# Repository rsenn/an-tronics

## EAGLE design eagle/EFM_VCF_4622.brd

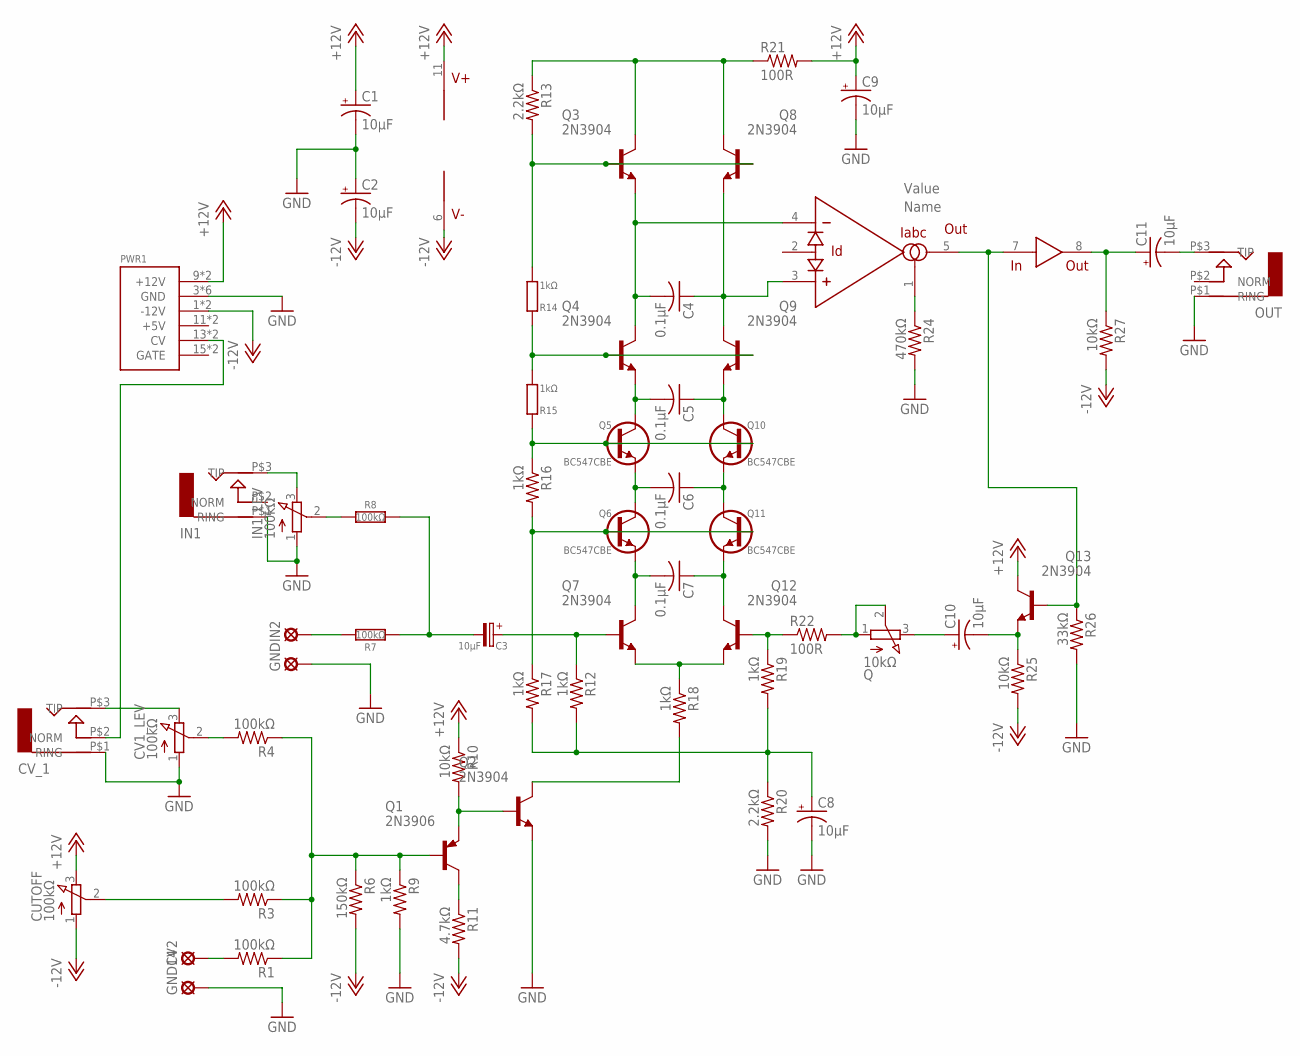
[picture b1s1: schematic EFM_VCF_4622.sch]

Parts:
C1, C2, C8, C9: 10μF; B45181A
C3: 10μF; E2,5-4
C4, C5, C6, C7: 0.1μF; C050-025X075
C10: 10μF; B45181C
C11: 10μF; B45181B
CUTOFF: 100kΩ; 3RP/1610N
CV1_LEV: 100kΩ; 3RP/1610N
CV2: LSP10
CV_1: AUDIO-JACK; ERTHENVAR-JACK-90DEG
GND, GND14: LSP10
IC1: LM13700N; DIL16
IN1: AUDIO-JACK; ERTHENVAR-JACK-90DEG
IN1_LEV: 100kΩ; 3RP/1610N
IN2: LSP10
OUT: AUDIO-JACK; ERTHENVAR-JACK-90DEG
PWR1: POWER; POWER_16
Q: 10kΩ; 3RP/1610N
Q1: 2N3906; TO92
Q2, Q3, Q4, Q7, Q8, Q9, Q12, Q13: 2N3904; TO92
Q5, Q6, Q10, Q11: BC547CBE; TO92-CBE
R1, R3, R4: 100kΩ; 0207/7
R6: 150kΩ; 0207/7
R7, R8: 100kΩ; 0204/10
R9, R12, R16, R17, R18, R19: 1kΩ; 0207/7
R10, R25, R27: 10kΩ; 0207/7
R11: 4.7kΩ; 0207/7
R13, R20: 2.2kΩ; 0207/7
R14, R15: 1kΩ; 0204/10-V
R21, R22: 100R; 0207/7
R24: 470kΩ; 0207/7
R26: 33kΩ; 0207/7

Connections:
+12V: C1.+, C9.+, CUTOFF.3 (E), IC1.11 (V+), PWR1.9 (+12V), PWR1.10 (+12V), Q13.1 (C), R10.1, R21.2
-12V: C2.-, CUTOFF.1 (A), IC1.6 (V-), PWR1.1 (-12V), PWR1.2 (-12V), R6.2, R11.2, R25.2, R27.2
GND: C1.-, C2.+, C8.-, C9.-, CV1_LEV.1 (A), CV_1.P$1 (RING), GND.MP, GND14.MP, IN1.P$1 (RING), IN1_LEV.1 (A), OUT.P$1 (RING), PWR1.3 (GND), PWR1.4 (GND), PWR1.5 (GND), PWR1.6 (GND), PWR1.7 (GND), PWR1.8 (GND), Q2.3 (E), R9.2, R20.2, R24.2, R26.2
unnamed: IC1.1 (IABC), R24.1
unnamed: Q.1 (A), Q.2 (S), R22.2
unnamed: Q2.1 (C), R18.2
unnamed: Q7.3 (E), Q12.3 (E), R18.1
unnamed: IN2.MP, R7.2
unnamed: C3.-, R7.1, R8.2
unnamed: C3.+, Q7.2 (B), R12.1
unnamed: Q1.3 (E), Q2.2 (B), R10.2
unnamed: C4.2, IC1.4 (-IN), Q3.3 (E), Q4.1 (C)
unnamed: C10.+, Q.3 (E)
unnamed: CV2.MP, R1.2
unnamed: C4.1, IC1.3 (+IN), Q8.3 (E), Q9.1 (C)
unnamed: C6.1, Q10.E, Q11.C
unnamed: C5.2, Q4.3 (E), Q5.C
unnamed: C5.1, Q9.3 (E), Q10.C
unnamed: C7.1, Q11.E, Q12.1 (C)
unnamed: C7.2, Q6.E, Q7.1 (C)
unnamed: IC1.5 (OUT), IC1.7 (IN), Q13.2 (B), R26.1
unnamed: Q1.2 (B), R1.1, R3.1, R4.1, R6.1, R9.1
unnamed: C8.+, R12.2, R17.2, R19.2, R20.1
unnamed: Q12.2 (B), R19.1, R22.1
unnamed: Q1.1 (C), R11.1
unnamed: C11.+, IC1.8 (OUT), R27.1
unnamed: C6.2, Q5.E, Q6.C
unnamed: C11.-, OUT.P$3 (TIP)
unnamed: C10.-, Q13.3 (E), R25.1
unnamed: Q3.1 (C), Q8.1 (C), R13.1, R21.1
unnamed: Q3.2 (B), Q8.2 (B), R13.2, R14.2 (1)
unnamed: Q4.2 (B), Q9.2 (B), R14.1 (2), R15.2 (1)
unnamed: Q5.B, Q10.B, R15.1 (2), R16.1
unnamed: Q6.B, Q11.B, R16.2, R17.1
unnamed: CV1_LEV.2 (S), R4.2
unnamed: CV_1.P$2 (NORM), PWR1.13 (CV), PWR1.14 (CV)
unnamed: CUTOFF.2 (S), R3.2
unnamed: IN1_LEV.2 (S), R8.1
unnamed: IN1.P$3 (TIP), IN1_LEV.3 (E)
unnamed: CV1_LEV.3 (E), CV_1.P$3 (TIP)

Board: 2 copper layers, 61 parts (0 on the bottom side), 40 nets, no tracks yet.

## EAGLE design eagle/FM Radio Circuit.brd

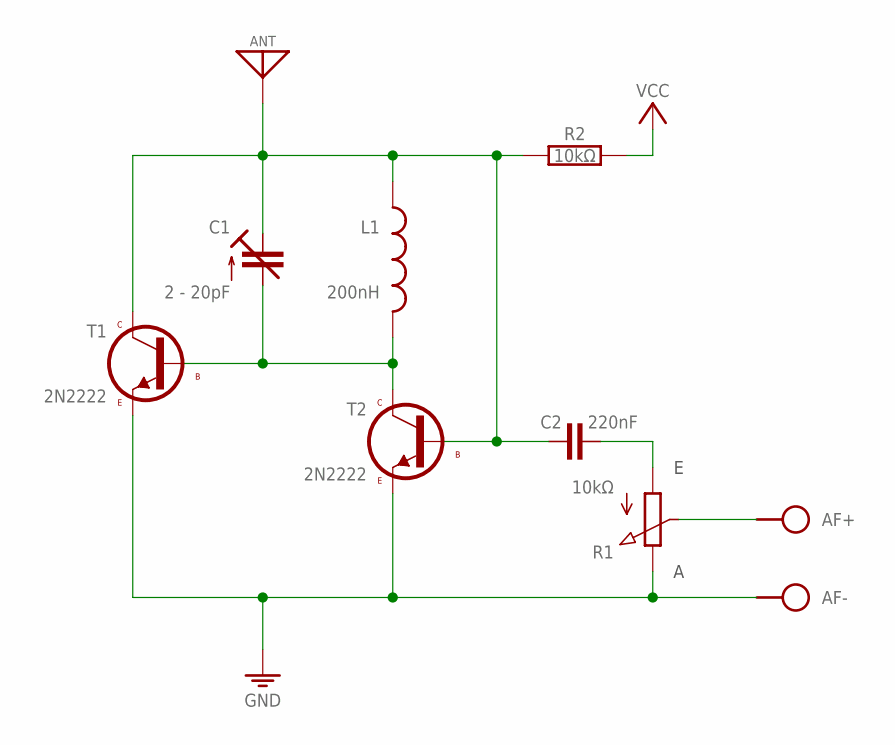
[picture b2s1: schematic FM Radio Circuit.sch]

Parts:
AF: SPAD+-+-; SPAD+-
ANT: ANT; SPAD
BAT: VCC_GNDL; SPAD-+
C1: 2 - 20pF; TRIM-2222-808
C2: 220nF; C050-020X044
L1: 200nH; L-04/7-V
R1: 10kΩ; POT
R2: 10kΩ; 0204/10
T1, T2: 2N2222; TO92-EBC

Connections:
GND: AF.1, BAT.1 (GND), R1.E, T1.E, T2.E
unnamed: C1.2 (A), L1.2, T1.B, T2.C
unnamed: C2.2, R1.A
unnamed: ANT.1, C1.3 (E), C2.1, L1.1, R2.1, T1.C, T2.B
unnamed: AF.2, R1.S
VCC: BAT.2 (VCC), R2.2

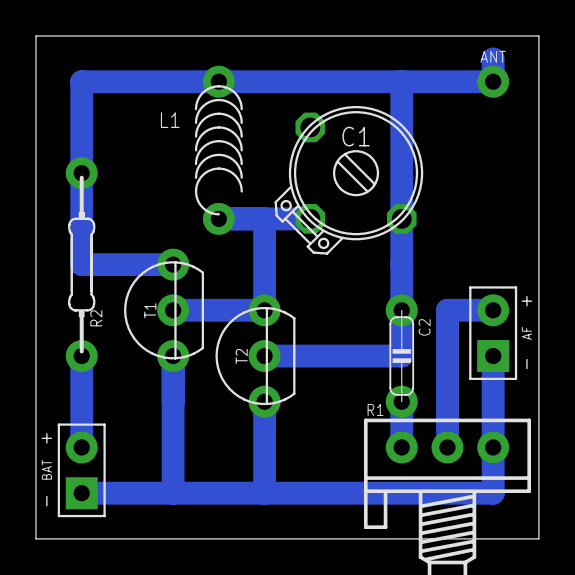
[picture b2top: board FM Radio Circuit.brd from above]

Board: 2 copper layers, 27.9 x 27.9 mm, 10 parts (0 on the bottom side), 6 nets.

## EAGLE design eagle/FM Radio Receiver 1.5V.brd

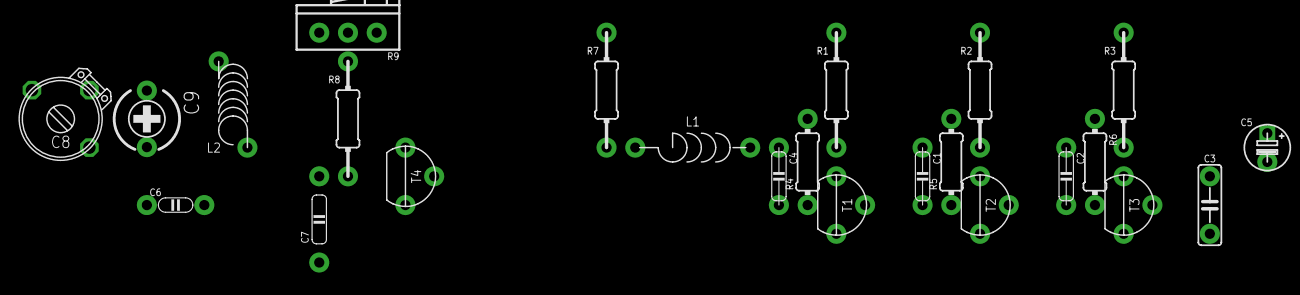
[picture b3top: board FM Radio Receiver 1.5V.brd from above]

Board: 2 copper layers, 24 parts (0 on the bottom side), 14 nets, no tracks yet.

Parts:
C1, C2: C050-020X044
C3: 10nF; C050-025X060
C4: 10nF; C050-020X044
C5: 100μF; E2.5-4/V
C6: 22pF; C050-020X036
C7: 100nF; C075-020X044
C8: 20pF; TRIM-2222-808
C9: 5pF; CTRIMTZ03
L1: 2.2μH; L-03/10
L2: L-04/8V
R1, R2: 4.7kΩ; 0204/10-V
R3: 0204/10-V
R4, R5: 1MΩ; 0204/7
R6: 56kΩ; 0204/7
R7: 10kΩ; 0204/10-V
R8: 470kΩ; 0204/10-V
R9: 10kΩ; POT
T1, T2, T3, T4: TO92-CBE-A

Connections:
unnamed: C1.2, R5.1, T2.2
unnamed: C2.1, R2.2, R5.2, T2.1
unnamed: C1.1, R1.2, R4.2, T1.1
unnamed: C2.2, R6.1, T3.2
unnamed: C3.1, R3.2, R6.2, T3.1
unnamed: C4.2, R4.1, T1.2
unnamed: C4.1, L1.1
unnamed: C5.+, R1.1, R2.1, R3.1, R7.1, R9.A
unnamed: C7.2, R8.2, T4.2
unnamed: R8.1, R9.S
unnamed: C8.2, C9.2, L2.2, T4.1
unnamed: C6.2, C7.1, L1.2, L2.1, R7.2
unnamed: C6.1, C8.1, C9.1
unnamed: C3.2, C5.-, R9.E, T1.3, T2.3, T3.3, T4.3

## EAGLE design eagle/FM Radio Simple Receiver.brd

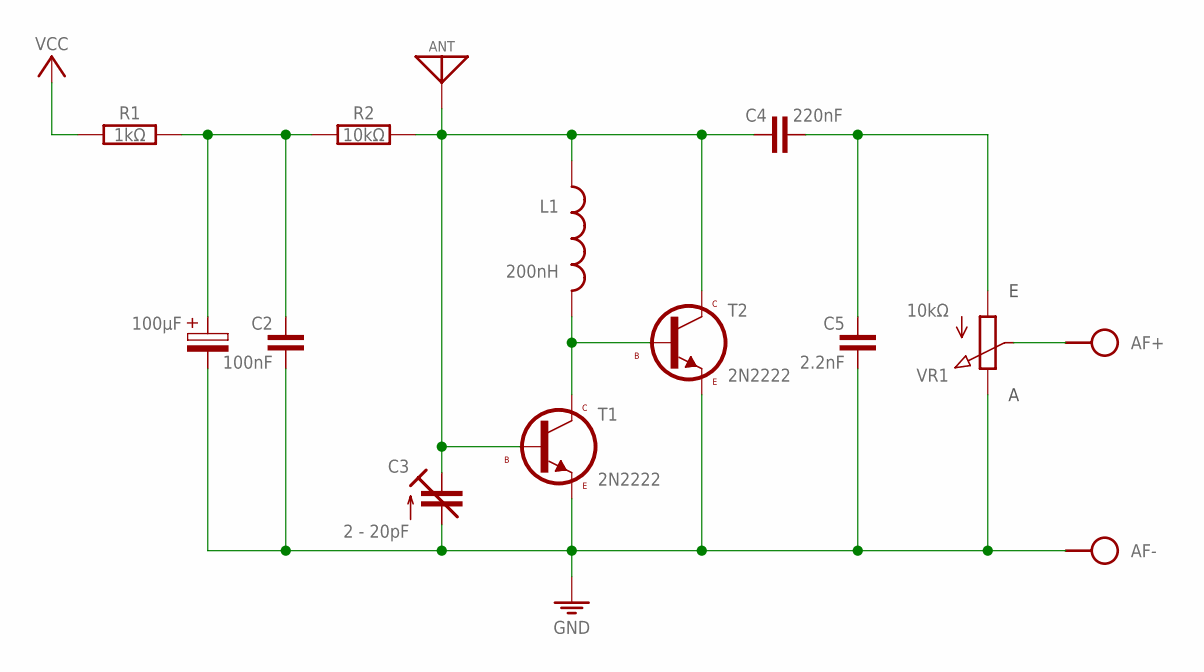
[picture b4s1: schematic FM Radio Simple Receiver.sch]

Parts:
100µF: CPOLE2,5-5/V; E2,5-5/V
AF: SPAD+-+-; SPAD+-
ANT: ANT; SPAD
BAT: VCC_GNDL; SPAD-+
C2: 100nF; C050-020X036/V
C3: 2 - 20pF; TRIM-2222-808
C4: 220nF; C050-020X044
C5: 2.2nF; C050-020X036/V
L1: 200nH; L-04/7-V
R1: 1kΩ; 0204/10
R2: 10kΩ; 0204/10
T1, T2: 2N2222; TO92-EBC
VR1: 10kΩ; POT

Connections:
GND: 100µF.-, AF.1, BAT.1 (GND), C2.2, C3.1 (A), C3.3 (A), C5.2, T1.E, T2.E, VR1.E
unnamed: ANT.1, C3.2 (E), C4.1, L1.1, R2.2, T1.B, T2.C
unnamed: 100µF.+, C2.1, R1.2, R2.1
unnamed: C4.2, C5.1, VR1.A
unnamed: L1.2, T1.C, T2.B
unnamed: AF.2, VR1.S
VCC: BAT.2 (VCC), R1.1

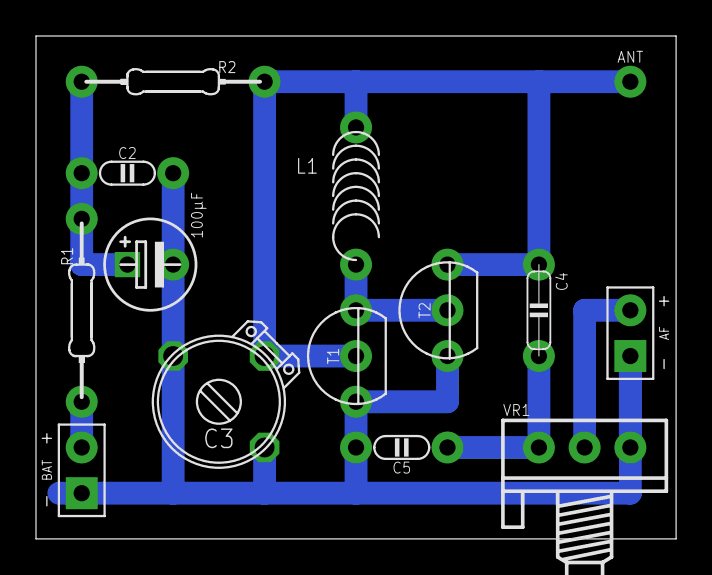
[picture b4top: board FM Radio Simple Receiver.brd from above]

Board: 2 copper layers, 35.6 x 27.9 mm, 14 parts (0 on the bottom side), 7 nets.

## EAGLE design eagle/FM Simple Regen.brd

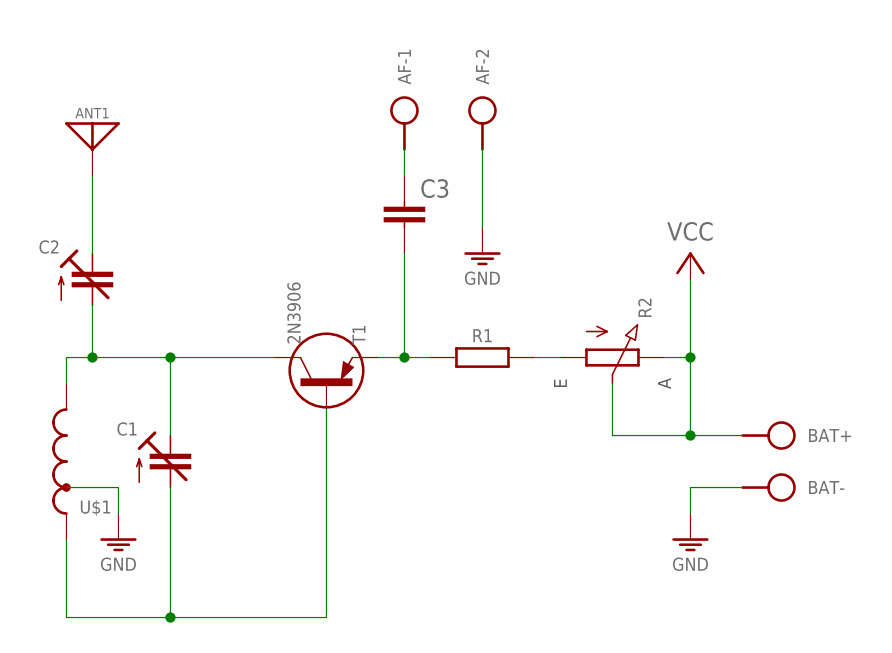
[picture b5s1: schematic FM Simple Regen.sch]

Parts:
AF: SPAD-2
ANT1: ANT; SPAD
BAT+: SPAD
BAT-: SPAD
C1: C-TR-PH201272222-808-2PINB; TRIM-2222-808
C2: C-TR-PH201272222-808-2PIN; TRIM-2222-808
C3: C050-024X044
R1: R-H0204/10; 0204/10
R2: POT
T1: 2N3906; TO92
U$1: L-TAP104/7; L-04/7-TAP1

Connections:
GND: AF.2, BAT-.1, U$1.T
unnamed: C1.2 (A), T1.2 (B), U$1.1
unnamed: AF.1, C3.1
unnamed: C1.3 (E), C2.2 (A), T1.3 (C), U$1.2
unnamed: C3.2, R1.1, T1.1 (E)
unnamed: R1.2, R2.A
unnamed: ANT1.1, C2.1 (E)
VCC: BAT+.1, R2.E, R2.S

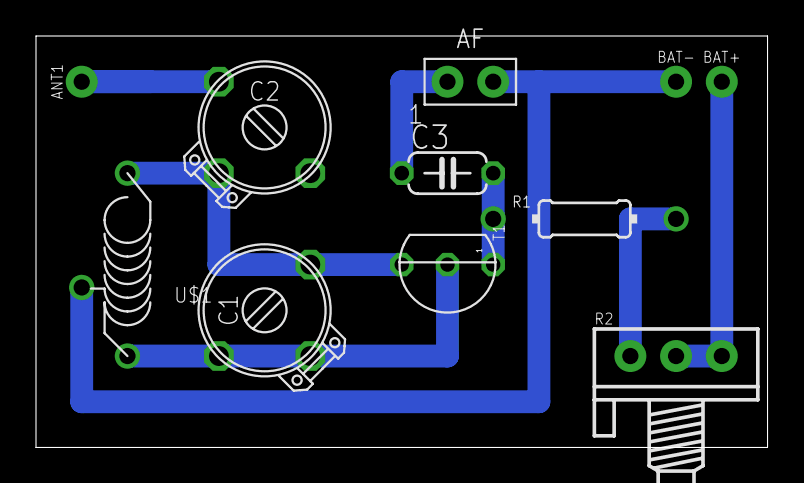
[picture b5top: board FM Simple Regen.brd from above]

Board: 2 copper layers, 40.6 x 22.9 mm, 11 parts (0 on the bottom side), 8 nets.

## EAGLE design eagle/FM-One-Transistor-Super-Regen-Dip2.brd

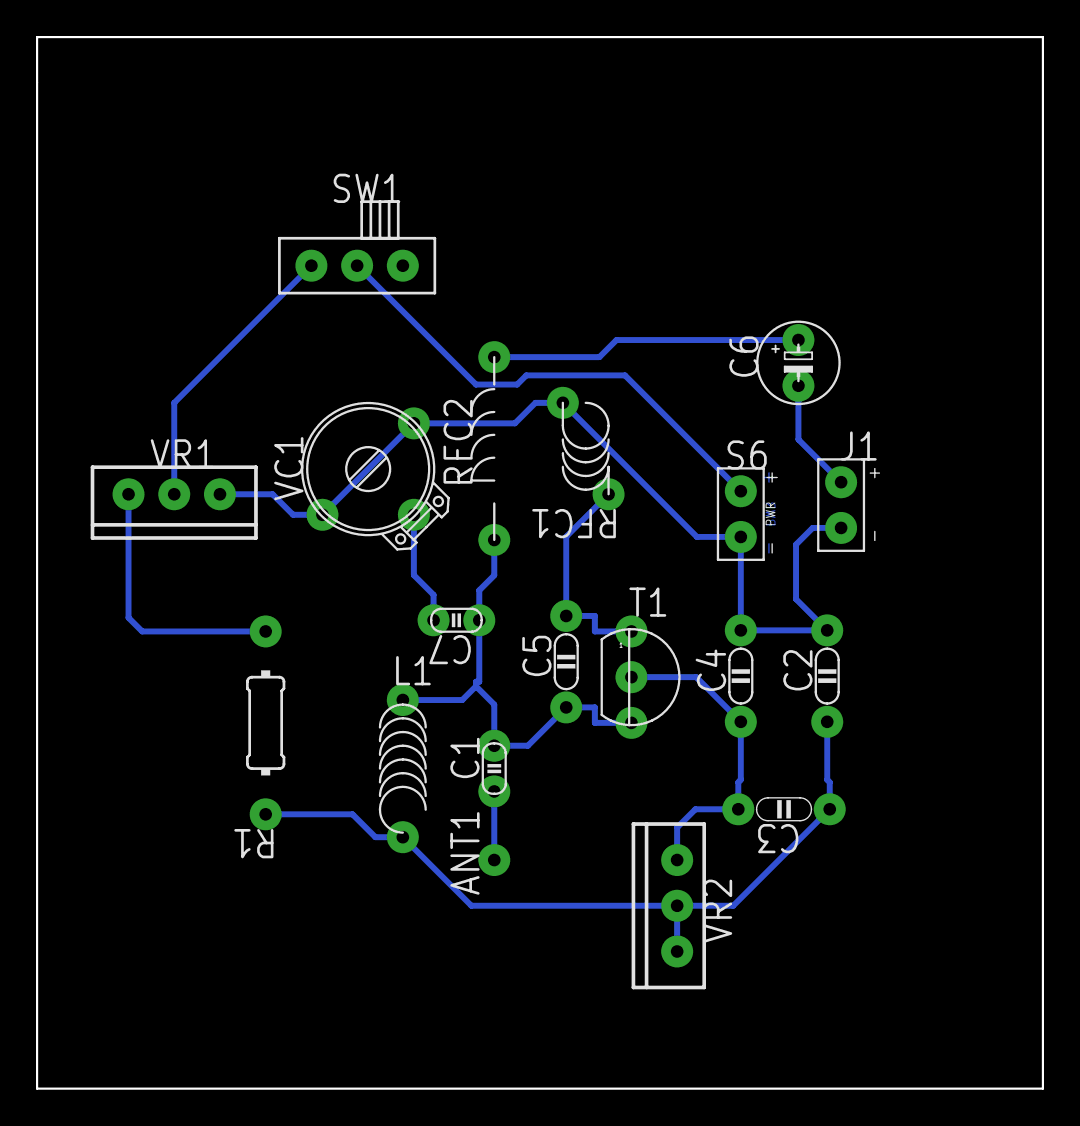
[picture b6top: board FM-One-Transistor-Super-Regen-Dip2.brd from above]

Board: 2 copper layers, 55.9 x 58.4 mm, 19 parts (0 on the bottom side), 12 nets.

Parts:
ANT1: ANT; SPAD
C1: 5pF; C025-015X024
C2: 0.001; C050-020X036/V
C3: 0.001; C050-020X036
C4: 100pF; C050-020X036/V
C5: 10pF; C050-020X036/V
C6: 10µF; E2,5-4
C7: 47pF; C025-015X024
J1: SPAD+-+-; SPAD+-
L1: 4t; L-04/7-V
R1: 2.2kΩ; 0204/10-V
RFC1: 10µH; L-04-2/5V
RFC2: 10µH; L-03/10
S6: VCC_GNDPWR-R; PWR-R
SW1: SW-SPST-SL-1P2T-H; SLSW-1P2T-H
T1: 2N3904; TO92
VC1: 20pF; TRIM-2222-808
VR1: 10kΩ; TRIM-POT
VR2: 100kΩ; TRIM-POT

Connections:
GND: C2.2, C4.2, J1.1, RFC1.1, S6.1, VC1.1, VC1.3, VR1.E
unnamed: ANT1.1, C1.1
unnamed: C1.2, C5.1, C7.1, L1.1, RFC2.2, T1.3
unnamed: C2.1, C3.1, L1.2, R1.1, VR2.E, VR2.S
unnamed: C7.2, VC1.2
unnamed: R1.2, VR1.A
unnamed: C5.2, RFC1.2, T1.1
unnamed: C3.2, C4.1, T1.2, VR2.A
unnamed: SW1.S, VR1.S
unnamed: C6.+, RFC2.1
unnamed: C6.-, J1.2
VCC: S6.2, SW1.P

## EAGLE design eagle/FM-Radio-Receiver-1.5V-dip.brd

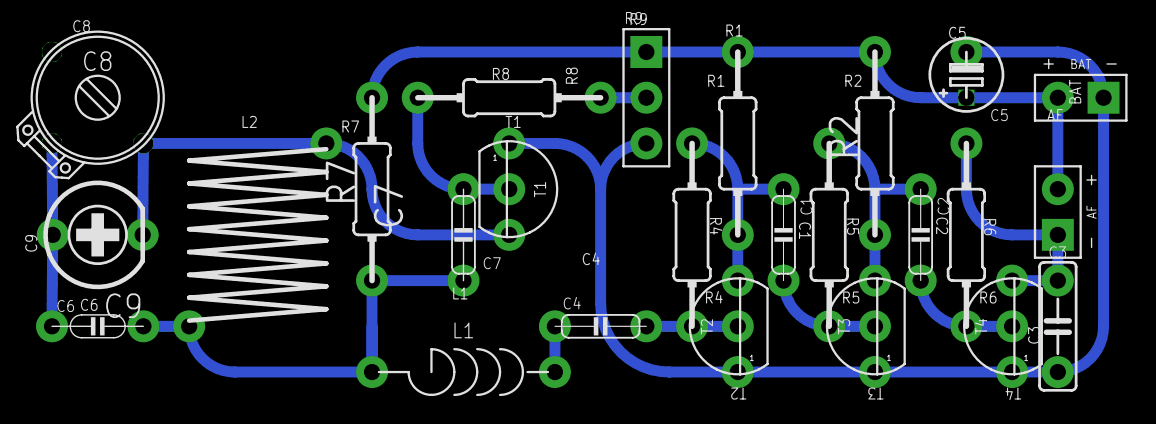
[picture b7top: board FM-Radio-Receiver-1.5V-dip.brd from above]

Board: 2 copper layers, 25 parts (0 on the bottom side), 14 nets.

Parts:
AF: SPAD+-+-; SPAD+-
BAT: SPAD+-+-; SPAD+-
C1: 33nF; C050-020X044
C2: 100nF; C050-020X044
C3: 10nF; C050-025X060
C4: 10nF; C050-020X044
C5: 100μF; E2.5-4/V
C6: 22pF; C050-020X036
C7: 100nF; C050-020X044/V
C8: 20pF; TRIM-2222-808
C9: 5pF; CTRIMTZ03
L1: 2.2μH; L-03/10
L2: 0.2μH; L-10/10Y
R1, R2: 4.7kΩ; 0204/10-V
R4, R5: 1MΩ; 0204/10-V
R6: 56kΩ; 0204/10-V
R7: 10kΩ; 0204/10-V
R8: 470kΩ; 0204/10-V
R9: 10kΩ; CONN-3P
T1, T2, T3, T4: 2N2222; TO92

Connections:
unnamed: C1.2, R5.1, T3.2
unnamed: C2.1, R2.2, R5.2, T3.3
unnamed: C1.1, R1.2, R4.2, T2.3
unnamed: C2.2, R6.1, T4.2
unnamed: AF.1, C3.1, R6.2, T4.3
unnamed: C4.2, R4.1, T2.2
unnamed: C4.1, L1.1
unnamed: AF.2, BAT.2, C5.+, R1.1, R2.1, R7.1, R9.1
unnamed: C7.2, R8.2, T1.2
unnamed: R8.1, R9.2
unnamed: C8.3, C9.2, L2.P$1, T1.3
unnamed: C6.2, C7.1, L1.2, L2.P$2, R7.2
unnamed: C6.1, C8.2, C9.1
unnamed: BAT.1, C3.2, C5.-, R9.3, T1.1, T2.1, T3.1, T4.1
